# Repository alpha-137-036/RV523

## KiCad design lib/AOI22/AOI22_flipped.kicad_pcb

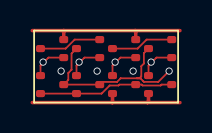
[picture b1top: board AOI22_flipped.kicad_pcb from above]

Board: 2 copper layers, 8 parts (0 on the bottom side), 10 nets.

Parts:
N1, N2, N3, N4: NMOS; SOT523
P1, P2, P3, P4: PMOS; SOT523

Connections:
A1: N1.1 (G), P1.1 (G)
A2: N2.1 (G), P2.1 (G)
B1: N3.1 (G), P3.1 (G)
B2: N4.1 (G), P4.1 (G)
GND: N1.2 (S), N3.2 (S)
VDD: P3.2 (S), P4.2 (S)
Y: N2.3 (D), N4.3 (D), P1.3 (D), P2.3 (D)
intA: N1.3 (D), N2.2 (S)
intB: N3.3 (D), N4.2 (S)
intP: P1.2 (S), P2.2 (S), P3.3 (D), P4.3 (D)

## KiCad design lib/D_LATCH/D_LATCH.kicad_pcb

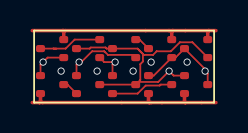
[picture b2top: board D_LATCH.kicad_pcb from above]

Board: 2 copper layers, 10 parts (0 on the bottom side), 11 nets.

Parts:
NOT1.N1, NOT1.N2, NOT2.N1, NOT3.N1, NOT3.N2: NMOS; SOT523
NOT1.P1, NOT1.P2, NOT2.P1, NOT3.P1, NOT3.P2: PMOS; SOT523

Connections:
CLK: NOT1.N2.1 (G), NOT3.P2.1 (G)
D: NOT1.N1.1 (G), NOT1.P1.1 (G)
GND: NOT1.N1.2 (S), NOT2.N1.2 (S), NOT3.N1.2 (S)
NOT1.intN: NOT1.N1.3 (D), NOT1.N2.2 (S)
NOT1.intP: NOT1.P1.3 (D), NOT1.P2.2 (S)
NOT3.intN: NOT3.N1.3 (D), NOT3.N2.2 (S)
NOT3.intP: NOT3.P1.3 (D), NOT3.P2.2 (S)
Q: NOT2.N1.3 (D), NOT2.P1.3 (D), NOT3.N1.1 (G), NOT3.P1.1 (G)
VDD: NOT1.P1.2 (S), NOT2.P1.2 (S), NOT3.P1.2 (S)
nCLK: NOT1.P2.1 (G), NOT3.N2.1 (G)
nQ: NOT1.N2.3 (D), NOT1.P2.3 (D), NOT2.N1.1 (G), NOT2.P1.1 (G), NOT3.N2.3 (D), NOT3.P2.3 (D)

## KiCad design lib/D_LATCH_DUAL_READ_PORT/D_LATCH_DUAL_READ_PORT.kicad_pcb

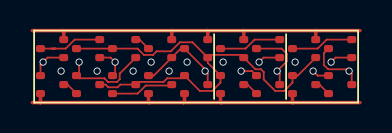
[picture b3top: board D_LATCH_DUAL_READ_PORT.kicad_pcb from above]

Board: 2 copper layers, 18 parts (0 on the bottom side), 17 nets.

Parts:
latch.NOT1.N1, latch.NOT1.N2, latch.NOT2.N1, latch.NOT3.N1, latch.NOT3.N2: NMOS; SOT523
latch.NOT1.P1, latch.NOT1.P2, latch.NOT2.P1, latch.NOT3.P1, latch.NOT3.P2: PMOS; SOT523
port1.N1, port1.N2, port2.N1, port2.N2: NMOS; SOT523
port1.P1, port1.P2, port2.P1, port2.P2: PMOS; SOT523

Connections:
CLK: latch.NOT1.N2.1 (G), latch.NOT3.P2.1 (G)
D: latch.NOT1.N1.1 (G), latch.NOT1.P1.1 (G)
GND: latch.NOT1.N1.2 (S), latch.NOT2.N1.2 (S), latch.NOT3.N1.2 (S), port1.N1.2 (S), port2.N1.2 (S)
Q: latch.NOT2.N1.3 (D), latch.NOT2.P1.3 (D), latch.NOT3.N1.1 (G), latch.NOT3.P1.1 (G)
Q1: port1.N2.3 (D), port1.P2.3 (D)
Q2: port2.N2.3 (D), port2.P2.3 (D)
VDD: latch.NOT1.P1.2 (S), latch.NOT2.P1.2 (S), latch.NOT3.P1.2 (S), port1.P1.2 (S), port2.P1.2 (S)
latch.NOT1.Y: latch.NOT1.N2.3 (D), latch.NOT1.P2.3 (D), latch.NOT2.N1.1 (G), latch.NOT2.P1.1 (G), latch.NOT3.N2.3 (D), latch.NOT3.P2.3 (D), port1.N1.1 (G), port1.P1.1 (G), port2.N1.1 (G), port2.P1.1 (G)
latch.NOT1.intN: latch.NOT1.N1.3 (D), latch.NOT1.N2.2 (S)
latch.NOT1.intP: latch.NOT1.P1.3 (D), latch.NOT1.P2.2 (S)
latch.NOT3.intN: latch.NOT3.N1.3 (D), latch.NOT3.N2.2 (S)
latch.NOT3.intP: latch.NOT3.P1.3 (D), latch.NOT3.P2.2 (S)
nCLK: latch.NOT1.P2.1 (G), latch.NOT3.N2.1 (G)
port1.intN: port1.N1.3 (D), port1.N2.2 (S)
port1.intP: port1.P1.3 (D), port1.P2.2 (S)
port2.intN: port2.N1.3 (D), port2.N2.2 (S)
port2.intP: port2.P1.3 (D), port2.P2.2 (S)
